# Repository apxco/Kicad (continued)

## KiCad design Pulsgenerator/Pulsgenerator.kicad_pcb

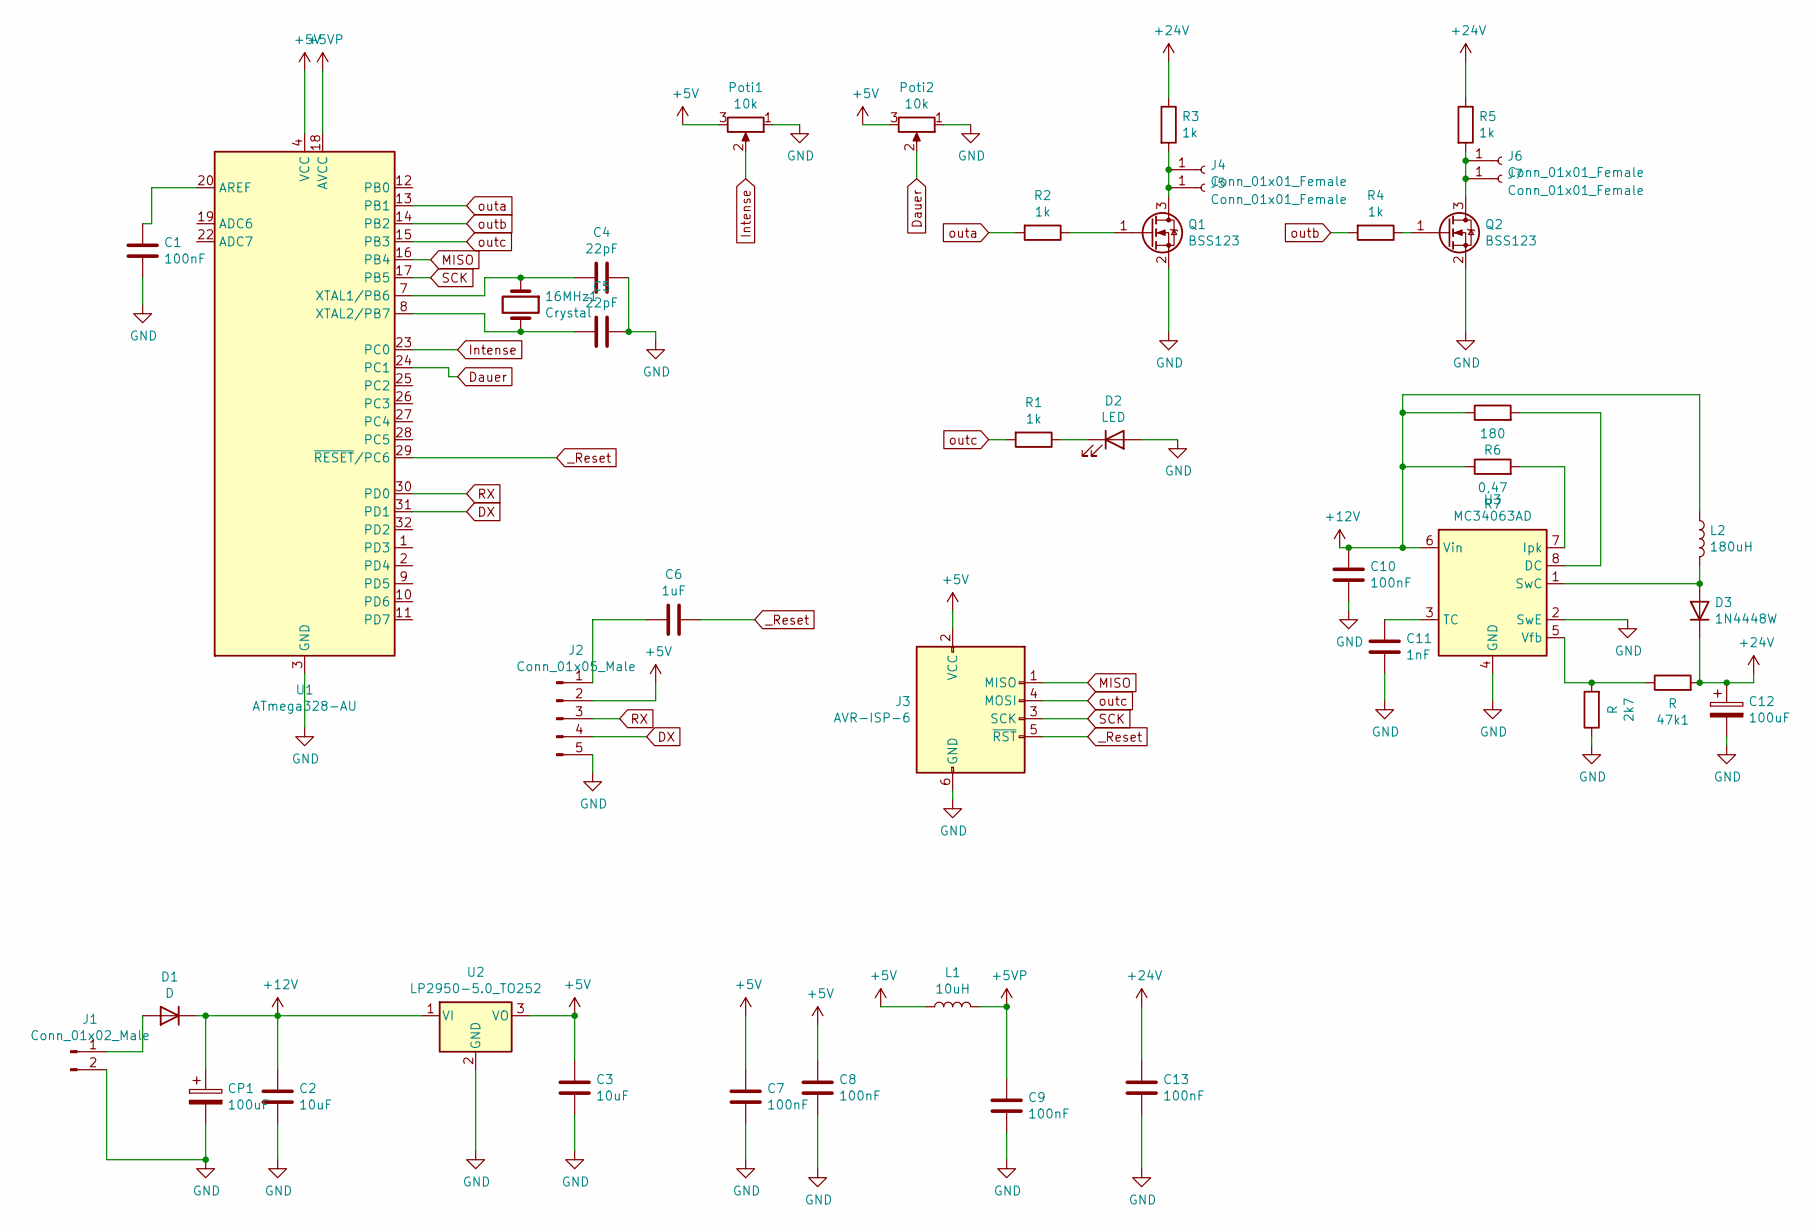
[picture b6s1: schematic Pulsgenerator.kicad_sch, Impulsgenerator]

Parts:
2k7, 47k1: R; R_0805_2012Metric_Pad1.15x1.40mm_HandSolder
16MHz1: Crystal; Crystal_HC18-U_Vertical
C1, C7, C8, C9, C10, C13: 100nF; C_0805_2012Metric_Pad1.15x1.40mm_HandSolder
C2, C3: 10uF; C_0805_2012Metric_Pad1.15x1.40mm_HandSolder
C4, C5: 22pF; C_0805_2012Metric_Pad1.15x1.40mm_HandSolder
C6: 1uF; C_0805_2012Metric_Pad1.15x1.40mm_HandSolder
C11: 1nF; C_0805_2012Metric_Pad1.15x1.40mm_HandSolder
C12: 100uF; CP_Elec_8x10
CP1: 100uF; CP_Elec_8x10
D1: D; D_5W_P10.16mm_Horizontal
D2: LED; LED_0805_2012Metric_Pad1.15x1.40mm_HandSolder
D3: 1N4448W; D_SOD-123
J1: Conn_01x02_Male; PhoenixContact_MSTBVA_2,5_2-G-5,08_1x02_P5.08mm_Vertical
J2: Conn_01x05_Male; PinHeader_1x05_P2.54mm_Vertical
J3: AVR-ISP-6; PinHeader_2x03_P2.54mm_Vertical
J4, J5, J6, J7: Conn_01x01_Female; IHI_B6A-PCB-45_Vertical
L1: 10uH; L_Wuerth_MAPI-3020
L2: 180uH; L_Taiyo-Yuden_NR-80xx_HandSoldering
Poti1, Poti2: 10k; Potentiometer_Alps_RK09L_Single_Vertical
Q1, Q2: BSS123; SOT-23
R1, R2, R3, R4, R5: 1k; R_0805_2012Metric_Pad1.15x1.40mm_HandSolder
R6: 180; R_0805_2012Metric_Pad1.15x1.40mm_HandSolder
R7: 0,47; R_1210_3225Metric_Pad1.42x2.65mm_HandSolder
U1: ATmega328-AU; TQFP-32_7x7mm_P0.8mm
U2: LP2950-5.0_TO252; TO-252-2
U3: MC34063AD; SOIC-8_3.9x4.9mm_P1.27mm

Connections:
+5V: C3.1, C7.1, C8.1, J2.2, J3.2 (VCC), L1.1, Poti1.3, Poti2.3, U1.4 (VCC), U1.6 (VCC), U2.3 (VO)
+5VP: C9.1, L1.2, U1.18 (AVCC)
+12V: C2.1, C10.1, CP1.1, D1.1 (K), L2.1, R6.1, R7.1, U2.1 (VI), U3.6 (Vin)
+24V: 47k1.2, C12.1, C13.1, D3.1 (K), R3.1, R5.1
DX: J2.4, U1.31 (PD1)
Dauer: Poti2.2, U1.24 (PC1)
GND: 2k7.1, C1.2, C2.2, C3.2, C4.1, C5.1, C7.2, C8.2, C9.2, C10.2, C11.2, C12.2, C13.2, CP1.2, D2.2 (A), J1.2, J2.5, J3.6 (GND), Poti1.1, Poti2.1, Q1.2 (S), Q2.2 (S), U1.3 (GND), U1.5 (GND), U1.21 (GND), U2.2 (GND), U3.2 (SwE), U3.4 (GND)
Intense: Poti1.2, U1.23 (PC0)
MISO: J3.1 (MISO), U1.16 (PB4)
unnamed: 2k7.2, 47k1.1, U3.5 (Vfb)
unnamed: 16MHz1.1, C4.2, U1.7 (XTAL1/PB6)
unnamed: 16MHz1.2, C5.2, U1.8 (XTAL2/PB7)
unnamed: C1.1, U1.20 (AREF)
unnamed: C6.2, J2.1
unnamed: C11.1, U3.3 (TC)
unnamed: D1.2 (A), J1.1
unnamed: D2.1 (K), R1.1
unnamed: D3.2 (A), L2.2, U3.1 (SwC)
unnamed: J4.1, J5.1, Q1.3 (D), R3.2
unnamed: J6.1, J7.1, Q2.3 (D), R5.2
unnamed: Q1.1 (G), R2.1
unnamed: Q2.1 (G), R4.1
unnamed: R6.2, U3.8 (DC)
unnamed: R7.2, U3.7 (Ipk)
RX: J2.3, U1.30 (PD0)
SCK: J3.3 (SCK), U1.17 (PB5)
_Reset: C6.1, J3.5 (~RST), U1.29 (~RESET/PC6)
outa: R2.2, U1.13 (PB1)
outb: R4.2, U1.14 (PB2)
outc: J3.4 (MOSI), R1.2, U1.15 (PB3)

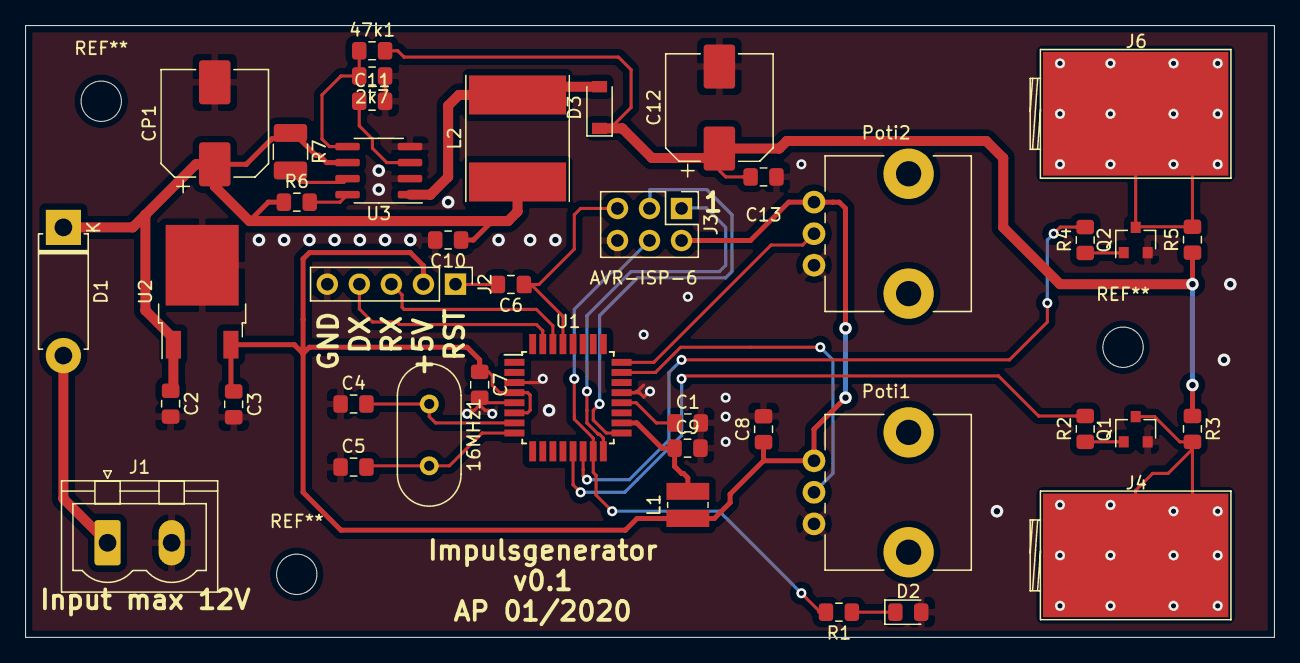
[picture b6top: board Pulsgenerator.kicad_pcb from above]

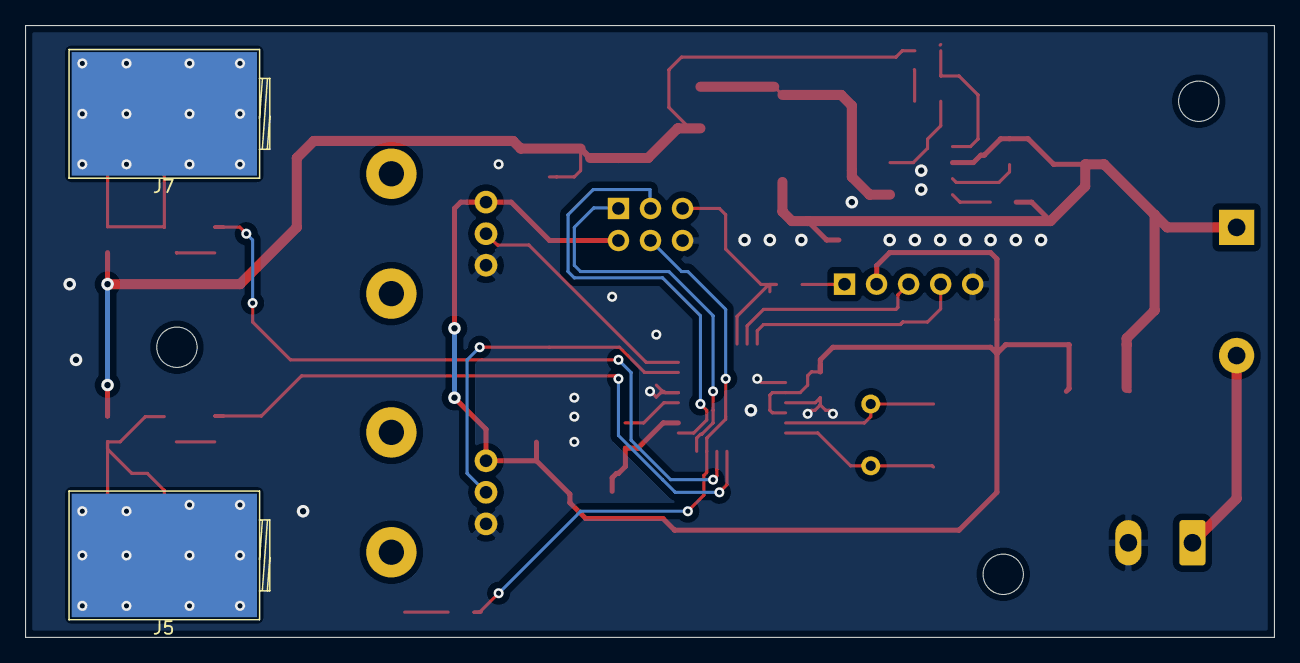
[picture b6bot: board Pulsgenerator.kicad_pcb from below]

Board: 2 copper layers, 99.0 x 48.5 mm, 43 parts (2 on the bottom side), 30 nets.
